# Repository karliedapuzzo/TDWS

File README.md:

# TDWS
Senior Project 2024-25: Train Detection and Warning System.<br>

Made by Raphael Jara and Karlie D'Apuzzo

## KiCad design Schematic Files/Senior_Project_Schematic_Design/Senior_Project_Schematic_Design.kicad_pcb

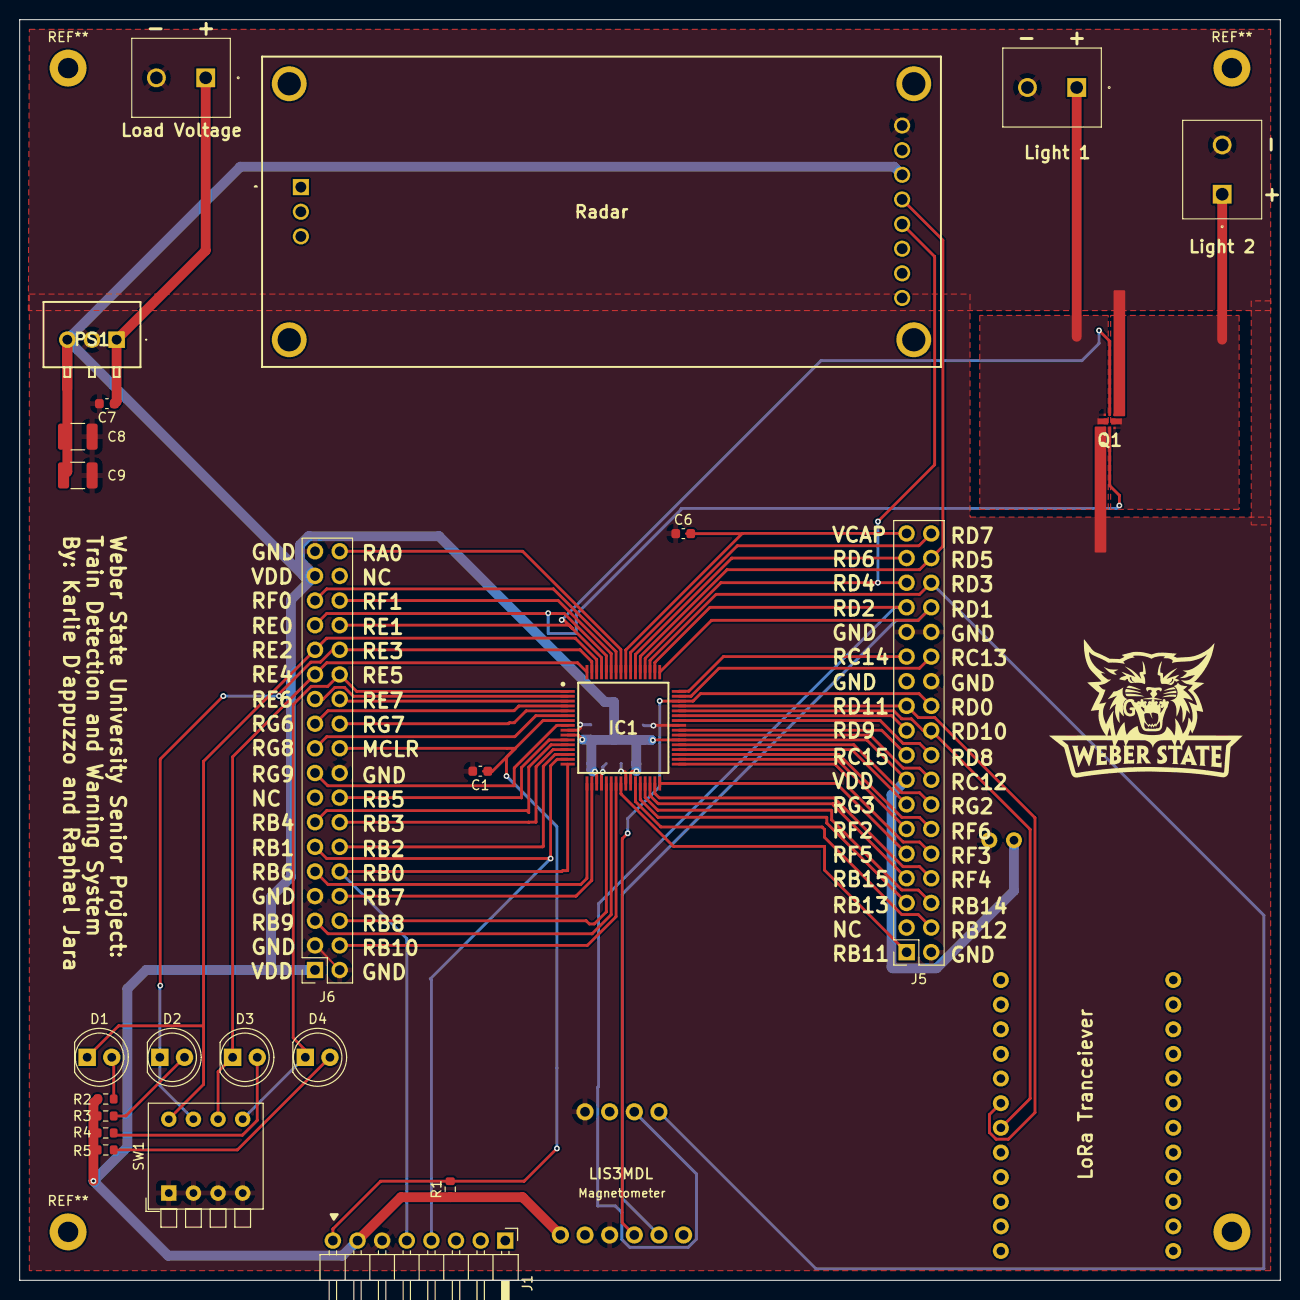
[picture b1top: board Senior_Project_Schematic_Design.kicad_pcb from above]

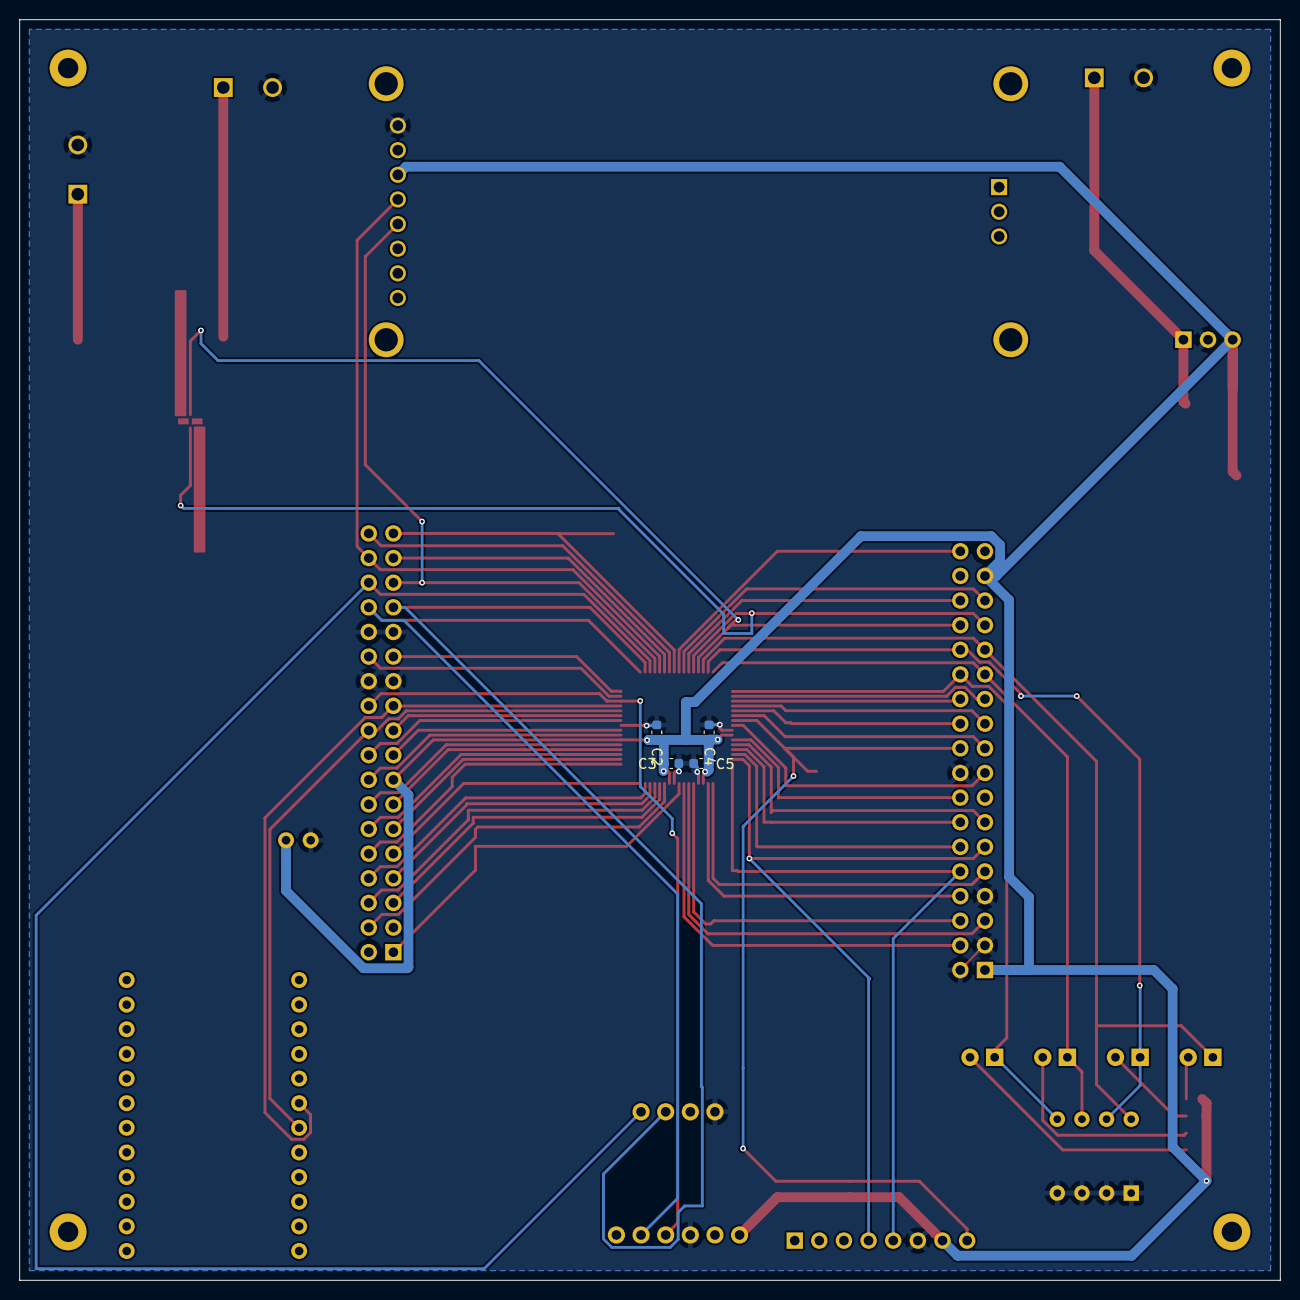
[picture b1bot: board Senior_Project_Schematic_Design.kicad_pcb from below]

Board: 2 copper layers, 130.0 x 130.0 mm, 31 parts (4 on the bottom side), 65 nets.

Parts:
C1, C2, C3, C4, C5: 0.1 uF; C_0603_1608Metric
C6, C7: 10uF; C_0603_1608Metric
C8, C9: 47uF; C_1210_3225Metric
D1, D2, D3, D4: LED; LED_D5.0mm
IC1: PIC24FJ128GL306-I_PT; QFP50P1200X1200X120-64N
J1: Conn_01x08_Pin; PinHeader_1x08_P2.54mm_Horizontal
J5, J6: Conn_02x18_Odd_Even; PinSocket_2x18_P2.54mm_Vertical
Light 1, Light 2: 1729128
Load Voltage: 1729128
PS1: TPSM84203EAB
Q1: SIB912DK-T1-GE3; SIB912DKT1GE3
R1: 330ohm; R_0603_1608Metric
R2, R3, R4, R5: 1kohm; R_0603_1608Metric
Radar: K-MD7-RFB-00H-02; KMD7RFB00H02
SW1: SW_DIP_x04; SW_DIP_SPSTx04_Piano_10.8x11.72mm_W7.62mm_P2.54mm
U1: LIS3MDL_Breakout; LIS3MDL
U3: Wio-E5_mini

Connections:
12V: C7.1, Load Voltage.1, PS1.1 (VIN)
GND: C1.2, C2.1, C3.1, C4.1, C5.1, C6.1, C7.2, C8.1, C9.2, IC1.9 (VSS_1), IC1.20 (AVSS), IC1.25 (VSS_2), IC1.41 (VSS_3), J1.6, J5.2, J5.23, J5.24, J5.27, J5.28, J6.2, J6.3, J6.7, J6.18, J6.35, Light 1.2, Light 2.2, Load Voltage.2, PS1.2 (GND), Q1.1 (S1), Q1.4 (S2), Radar.B1 (GND), SW1.1, SW1.2, SW1.3, SW1.4, U1.3 (GND), U1.7 (GND), U3.C2 (-)
Light_1_Positive: Light 1.1, Q1.6 (D1_1), Q1.8 (D1_2)
Light_2_Positive: Light 2.1, Q1.3 (D2_1), Q1.7 (D2_2)
MCLR: C1.1, IC1.7 (~MCLR), J1.8, J6.20, R1.2
unnamed: D1.2 (A), R2.2
unnamed: D2.2 (A), R3.2
unnamed: D3.2 (A), R4.2
unnamed: D4.2 (A), R5.2
RA0: IC1.57 (AN16/RA0), J6.36
RB0: IC1.16 (PGD1/SEG7/VREF+/CVREF+/AN0/RP0/RB0), J1.5, J6.10
RB1: IC1.15 (PGC1/SEG6/CVREF-/AN1/AN1-/RP1/RB1), J1.4, J6.11
RB2: IC1.14 (SEG5/AN2/C2INB/RP13/RB2), J6.12
RB3: IC1.13 (SEG4/AN3/C2INA/RB3), J6.14
RB4: IC1.12 (PGD3/SEG3/AN4/C1INB/RP28/ASDA1/OCM1B/RB4), J6.13
RB5: IC1.11 (PGC3/SEG2/AN5/C1INA/RP18/ASCL1/OCM1A/RB5), J6.16
RB6: IC1.17 (PGC2/LCDBIAS3/AN6/RP6/RB6), J6.9
RB7: IC1.18 (PGD2/AN7/RP7/T1CK/RB7), J6.8
RB8: IC1.21 (COM7/SEG31/AN8/RP8/RB8), J6.6
RB9: IC1.22 (COM6/SEG30/AN9/RP9/RB9), J6.5
RB10: IC1.23 (TMS/COM5/SEG29/CVREF/AN10/RP15/RB10), J6.4
RB11: IC1.24 (TDO/AN11/RB11), J5.1
RB12: IC1.27 (TCK/SEG18/AN12/RB12), J5.4
RB13: IC1.28 (TDI/SEG19/AN13/RB13), J5.5
RB14: IC1.29 (SEG8/AN14/RP14/OCM1C/RB14), J5.6
RB15: IC1.30 (SEG9/AN15/RP29/OCM1D/RB15), J5.7
RC12: IC1.39 (OSCI/CLKI/RC12), J5.16
RC13: IC1.47 (SOSCI/RC13), J5.26
RC14: IC1.48 (SOSCO/SCLKI/RPI37/PWRLCLK/RC14), J5.25
RC15: IC1.40 (OSCO/CLKO/RC15), J5.17
RD0: IC1.46 (SEG17/RP11/RD0), J5.22, U1.4 (SCL)
RD1: IC1.49 (SEG20/RP24/RD1), J5.30, U1.5 (SDA)
RD2: IC1.50 (SEG21/RP23/RD2), J5.29, U1.9 (D0)
RD3: IC1.51 (SEG22/RP22/RD3), J5.32, U1.10 (CS)
RD4: IC1.52 (SEG23/RP25/RD4), J5.31, Radar.B5 (TX)
RD5: IC1.53 (SEG24/RP20/RD5), J5.34, Radar.B4 (RX)
RD6: IC1.54 (SEG25/C3INB/RD6), J5.33
RD7: IC1.55 (SEG26/C3INA/RD7), J5.36
RD8: IC1.42 (SEG13/RP2/RD8), J5.18
RD9: IC1.43 (SEG14/RP4/RD9), J5.19
RD10: IC1.44 (SEG15/C3IND/RP3/RD10), J5.20, U3.B6 (TX)
RD11: IC1.45 (SEG16/C3INC/RP12/RD11), J5.21, U3.B7 (RX)
RE0: IC1.60 (COM3/RE0), J6.29, Q1.2 (G1)
RE1: IC1.61 (COM2/RE1), J6.30, Q1.5 (G2)
RE2: D1.1 (K), IC1.62 (COM1/RE2), J6.27, SW1.8
RE3: D2.1 (K), IC1.63 (COM0/RE3), J6.28, SW1.7
RE4: D3.1 (K), IC1.64 (SEG63/HLVDIN/RE4), J6.25, SW1.6
RE5: D4.1 (K), IC1.1 (LCDBIAS2/RE5), J6.26, SW1.5
RE6: IC1.2 (LCDBIAS1/RE6), J6.23
RE7: IC1.3 (LCDBIAS0/RE7), J6.24
RF0: IC1.58 (SEG27/RF0), J6.31
RF1: IC1.59 (COM4/SEG48/OCM1E/RF1), J6.32
RF2: IC1.34 (SEG40/RP30/RF2), J5.11
RF3: IC1.33 (SEG12/RP16/RF3), J5.10
RF4: IC1.31 (SEG10/RP10/SDA2/RF4), J5.8
RF5: IC1.32 (SEG11/RP17/SCL2/RF5), J5.9
RF6: IC1.35 (RP5/INT0/RF6), J5.12
RG2: IC1.37 (SEG28/SCL1/RG2), J5.14
RG3: IC1.36 (SEG47/RP31/SDA1/OCM1F/RG3), J5.13
RG6: IC1.4 (SEG0/C1IND/RP21/RG6), J6.21
RG7: IC1.5 (VLCAP1/C1INC/C2INC/C3INC/RP26/RG7), J6.22
RG8: IC1.6 (VLCAP2/C2IND/RP19/RG8), J6.19
RG9: IC1.8 (SEG1/C2INC/RP27/RG9), J6.17
VCAP: C6.2, IC1.56 (VCAP), J5.35
VDD: C2.2, C3.2, C4.2, C5.2, C8.2, C9.1, IC1.10 (VDD_1), IC1.19 (AVDD), IC1.26 (VDD_2), IC1.38 (VDD_3), J1.7, J5.15, J6.1, J6.33, PS1.3 (VOUT), R1.1, R2.1, R3.1, R4.1, R5.1, Radar.B3 (VCC), U1.1 (VIN), U3.C1 (+)

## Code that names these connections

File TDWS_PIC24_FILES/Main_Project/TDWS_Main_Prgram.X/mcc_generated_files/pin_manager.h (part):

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*/
/**
  @Summary
    Sets the GPIO pin, RD0, high using LATD0.

  @Description
    Sets the GPIO pin, RD0, high using LATD0.

  @Preconditions
    The RD0 must be set to an output.
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#define SCK1OUT_SetHigh()          (_LATD0 = 1)
/**
  @Summary
    Sets the GPIO pin, RD0, low using LATD0.

  @Description
    Sets the GPIO pin, RD0, low using LATD0.

  @Preconditions
    The RD0 must be set to an output.
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#define SCK1OUT_SetLow()           (_LATD0 = 0)
/**
  @Summary
    Toggles the GPIO pin, RD0, using LATD0.

  @Description
    Toggles the GPIO pin, RD0, using LATD0.

  @Preconditions
    The RD0 must be set to an output.
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#define SCK1OUT_Toggle()           (_LATD0 ^= 1)
/**
  @Summary
    Reads the value of the GPIO pin, RD0.

  @Description
    Reads the value of the GPIO pin, RD0.

  @Preconditions
    None.
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    </code>

*/
#define SCK1OUT_GetValue()         _RD0
/**
  @Summary
    Configures the GPIO pin, RD0, as an input.

  @Description
    Configures the GPIO pin, RD0, as an input.

  @Preconditions
    None.
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#define SCK1OUT_SetDigitalInput()  (_TRISD0 = 1)
/**
  @Summary
    Configures the GPIO pin, RD0, as an output.

  @Description
    Configures the GPIO pin, RD0, as an output.

  @Preconditions
    None.
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#define SCK1OUT_SetDigitalOutput() (_TRISD0 = 0)
/**
  @Summary
    Sets the GPIO pin, RD1, high using LATD1.

  @Description
    Sets the GPIO pin, RD1, high using LATD1.

  @Preconditions
    The RD1 must be set to an output.
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#define SDO1_SetHigh()          (_LATD1 = 1)
/**
  @Summary
    Sets the GPIO pin, RD1, low using LATD1.

  @Description
    Sets the GPIO pin, RD1, low using LATD1.

  @Preconditions
    The RD1 must be set to an output.
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#define SDO1_SetLow()           (_LATD1 = 0)
/**
  @Summary
    Toggles the GPIO pin, RD1, using LATD1.

  @Description
    Toggles the GPIO pin, RD1, using LATD1.

  @Preconditions
    The RD1 must be set to an output.
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#define SDO1_Toggle()           (_LATD1 ^= 1)
/**
  @Summary
    Reads the value of the GPIO pin, RD1.

  @Description
    Reads the value of the GPIO pin, RD1.

  @Preconditions
    None.
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    </code>

*/
#define SDO1_GetValue()         _RD1
/**
  @Summary
    Configures the GPIO pin, RD1, as an input.

  @Description
    Configures the GPIO pin, RD1, as an input.

  @Preconditions
    None.
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#define SDO1_SetDigitalInput()  (_TRISD1 = 1)
/**
  @Summary
    Configures the GPIO pin, RD1, as an output.

  @Description
    Configures the GPIO pin, RD1, as an output.

  @Preconditions
    None.
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#define SDO1_SetDigitalOutput() (_TRISD1 = 0)
/**
  @Summary
    Sets the GPIO pin, RD2, high using LATD2.

  @Description
    Sets the GPIO pin, RD2, high using LATD2.

  @Preconditions
    The RD2 must be set to an output.
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#define SDI1_SetHigh()          (_LATD2 = 1)
/**
  @Summary
    Sets the GPIO pin, RD2, low using LATD2.

  @Description
    Sets the GPIO pin, RD2, low using LATD2.

  @Preconditions
    The RD2 must be set to an output.
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#define SDI1_SetLow()           (_LATD2 = 0)
/**
  @Summary
    Toggles the GPIO pin, RD2, using LATD2.

  @Description
    Toggles the GPIO pin, RD2, using LATD2.

  @Preconditions
    The RD2 must be set to an output.
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#define SDI1_Toggle()           (_LATD2 ^= 1)
/**
  @Summary
    Reads the value of the GPIO pin, RD2.

  @Description
    Reads the value of the GPIO pin, RD2.

  @Preconditions
    None.
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    </code>

*/
#define SDI1_GetValue()         _RD2
/**
  @Summary
    Configures the GPIO pin, RD2, as an input.

  @Description
    Configures the GPIO pin, RD2, as an input.

  @Preconditions
    None.
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#define SDI1_SetDigitalInput()  (_TRISD2 = 1)
/**
  @Summary
    Configures the GPIO pin, RD2, as an output.

  @Description
    Configures the GPIO pin, RD2, as an output.

  @Preconditions
    None.
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#define SDI1_SetDigitalOutput() (_TRISD2 = 0)
/**
  @Summary
    Sets the GPIO pin, RD3, high using LATD3.

  @Description
    Sets the GPIO pin, RD3, high using LATD3.

  @Preconditions
    The RD3 must be set to an output.
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#define SS1_SetHigh()          (_LATD3 = 1)
/**
  @Summary
    Sets the GPIO pin, RD3, low using LATD3.

  @Description
    Sets the GPIO pin, RD3, low using LATD3.

  @Preconditions
    The RD3 must be set to an output.
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#define SS1_SetLow()           (_LATD3 = 0)
/**
  @Summary
    Toggles the GPIO pin, RD3, using LATD3.

  @Description
    Toggles the GPIO pin, RD3, using LATD3.

  @Preconditions
    The RD3 must be set to an output.
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#define SS1_Toggle()           (_LATD3 ^= 1)
/**
  @Summary
    Reads the value of the GPIO pin, RD3.

  @Description
    Reads the value of the GPIO pin, RD3.

  @Preconditions
    None.
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    </code>

*/
#define SS1_GetValue()         _RD3
/**
  @Summary
    Configures the GPIO pin, RD3, as an input.

  @Description
    Configures the GPIO pin, RD3, as an input.

  @Preconditions
    None.
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#define SS1_SetDigitalInput()  (_TRISD3 = 1)
/**
  @Summary
    Configures the GPIO pin, RD3, as an output.

  @Description
    Configures the GPIO pin, RD3, as an output.

  @Preconditions
    None.
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#define SS1_SetDigitalOutput() (_TRISD3 = 0)
/**
  @Summary
    Sets the GPIO pin, RE0, high using LATE0.

  @Description
    Sets the GPIO pin, RE0, high using LATE0.

  @Preconditions
    The RE0 must be set to an output.
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#define IO_RE0_SetHigh()          (_LATE0 = 1)
/**
  @Summary
    Sets the GPIO pin, RE0, low using LATE0.

  @Description
    Sets the GPIO pin, RE0, low using LATE0.

  @Preconditions
    The RE0 must be set to an output.
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#define IO_RE0_SetLow()           (_LATE0 = 0)
/**
  @Summary
    Toggles the GPIO pin, RE0, using LATE0.

  @Description
    Toggles the GPIO pin, RE0, using LATE0.

  @Preconditions
    The RE0 must be set to an output.
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#define IO_RE0_Toggle()           (_LATE0 ^= 1)
/**
  @Summary
    Reads the value of the GPIO pin, RE0.

  @Description
    Reads the value of the GPIO pin, RE0.

  @Preconditions
    None.
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    </code>

*/
#define IO_RE0_GetValue()         _RE0
/**
  @Summary
    Configures the GPIO pin, RE0, as an input.

  @Description
    Configures the GPIO pin, RE0, as an input.

  @Preconditions
    None.
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#define IO_RE0_SetDigitalInput()  (_TRISE0 = 1)
/**
  @Summary
    Configures the GPIO pin, RE0, as an output.

  @Description
    Configures the GPIO pin, RE0, as an output.

  @Preconditions
    None.
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#define IO_RE0_SetDigitalOutput() (_TRISE0 = 0)
/**
  @Summary
    Sets the GPIO pin, RE1, high using LATE1.

  @Description
    Sets the GPIO pin, RE1, high using LATE1.

  @Preconditions
    The RE1 must be set to an output.
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#define IO_RE1_SetHigh()          (_LATE1 = 1)
/**
  @Summary
    Sets the GPIO pin, RE1, low using LATE1.

  @Description
    Sets the GPIO pin, RE1, low using LATE1.

  @Preconditions
    The RE1 must be set to an output.
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#define IO_RE1_SetLow()           (_LATE1 = 0)
/**
  @Summary
    Toggles the GPIO pin, RE1, using LATE1.

  @Description
    Toggles the GPIO pin, RE1, using LATE1.

  @Preconditions
    The RE1 must be set to an output.
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#define IO_RE1_Toggle()           (_LATE1 ^= 1)
/**
  @Summary
    Reads the value of the GPIO pin, RE1.

  @Description
    Reads the value of the GPIO pin, RE1.

  @Preconditions
    None.
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    </code>

*/
#define IO_RE1_GetValue()         _RE1
/**
  @Summary
    Configures the GPIO pin, RE1, as an input.

  @Description
    Configures the GPIO pin, RE1, as an input.

  @Preconditions
    None.
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#define IO_RE1_SetDigitalInput()  (_TRISE1 = 1)
/**
  @Summary
    Configures the GPIO pin, RE1, as an output.

  @Description
    Configures the GPIO pin, RE1, as an output.

  @Preconditions
    None.
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#define IO_RE1_SetDigitalOutput() (_TRISE1 = 0)
/**
  @Summary
    Sets the GPIO pin, RE2, high using LATE2.

  @Description
    Sets the GPIO pin, RE2, high using LATE2.

  @Preconditions
    The RE2 must be set to an output.
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#define IO_RE2_SetHigh()          (_LATE2 = 1)
/**
  @Summary
    Sets the GPIO pin, RE2, low using LATE2.

  @Description
    Sets the GPIO pin, RE2, low using LATE2.

  @Preconditions
    The RE2 must be set to an output.
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#define IO_RE2_SetLow()           (_LATE2 = 0)
/**
  @Summary
    Toggles the GPIO pin, RE2, using LATE2.

  @Description
    Toggles the GPIO pin, RE2, using LATE2.

  @Preconditions
    The RE2 must be set to an output.
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#define IO_RE2_Toggle()           (_LATE2 ^= 1)
/**
  @Summary
    Reads the value of the GPIO pin, RE2.

  @Description
    Reads the value of the GPIO pin, RE2.

  @Preconditions
    None.
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    </code>

*/
#define IO_RE2_GetValue()         _RE2
/**
  @Summary
    Configures the GPIO pin, RE2, as an input.

  @Description
    Configures the GPIO pin, RE2, as an input.

  @Preconditions
    None.
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#define IO_RE2_SetDigitalInput()  (_TRISE2 = 1)
/**
  @Summary
    Configures the GPIO pin, RE2, as an output.

  @Description
    Configures the GPIO pin, RE2, as an output.

  @Preconditions
    None.
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#define IO_RE2_SetDigitalOutput() (_TRISE2 = 0)
/**
  @Summary
    Sets the GPIO pin, RE3, high using LATE3.

  @Description
    Sets the GPIO pin, RE3, high using LATE3.
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
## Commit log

2024-10-10 inital commit of pic24 testing files
2024-10-10 fixed gitignore
2024-10-19 Adding the Radar
2024-10-19 changed range setting from 10m to 100m on radar
2025-01-01 changed file organization for main project
2025-01-01 integrated magnetometer functions into main project :D
2025-01-02 added lora functions
2025-01-07 working on lora receiver code... not working :/
2025-01-09 restarted lora receiver testing
2025-01-17 got the uart2 interrupt working yay, need to implement rest of receiver code
2025-01-17 WORKING? PERHAPS
2025-01-17 working nicely, just need to adjust some things to that it's more modular :D
2025-02-01 writing radar functions
2025-02-01 stuff
2025-02-02 started writing radar code
2025-02-08 lost all my files :)
2025-02-09 ahhh
2025-02-12 have a way to spit out radar data to uart 4
2025-02-15 radar stuff
2025-02-15 trying
2025-02-15 fixed perhaps?
2025-02-15 fixed
2025-02-15 idk anymore
2025-03-03 commiting radar code to main project file
2025-03-04 this works
2025-03-04 filter works I think
2025-03-04 changed up the filter a little bit
2025-03-05 LoRaReceiverTesting now works for both rx and tx, so will be implemented into the main
2025-03-05 idk why but when implemented the lora just don't worky... big sigh
2025-03-05 idk i'll fix it tomorrow
2025-03-06 beep boop
2025-03-08 ITS ALIVEED
2025-03-10 misc
2025-03-10 radar works in test, not in main
2025-03-14 fixed up the radar stuff
2025-03-15 wawa weewo, the detection module code is written, and all seems to function okayish
2025-03-17 added magnetometer detection test and also fixed the light test mode
2025-03-22 have to push before pull
2025-04-13 adjusted some radar settings
2025-04-16 added additional resources folder
2025-04-16 removed png that wasn't supposed to be uploaded
2025-04-16 added pcb schematic files
2025-04-16 added documentation pdf
2025-04-16 added user manual and additional charge controller manual

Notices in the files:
TDWS_PIC24_FILES/Main_Project/TDWS_Main_Prgram.X/mcc_generated_files/pin_manager.h:
(c) 2020 Microchip Technology Inc. and its subsidiaries. You may use this
